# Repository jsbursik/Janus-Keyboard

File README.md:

# Janus Split Ergonomic Keyboard

## Janus

From [Wikipedia](https://en.wikipedia.org/wiki/Janus) on the god Janus: "In ancient Roman religion and myth, Janus (/ˈdʒeɪnəs/ JAY-nəs; Latin: Ianvs [ˈi̯aːnʊs]) is the god of beginnings, gates, transitions, time, duality, doorways, passages, frames, and endings. He is usually depicted as having two faces. The month of January is named for Janus (Ianuarius). According to ancient Roman farmers' almanacs, Juno was mistaken as the tutelary deity of the month of January, but Juno is the tutelary deity of the month of June."

## Motivation

I designed this keyboard after ordering and assembling a [Piantor](https://github.com/beekeeb/piantor) and not really liking the switches and keycaps. After realizing choc switches don't use the normal "+" stems I'm used to and seeing that the choc stems are a bit niche for finding keycaps - I started looking for other low-profile switch options that supported the more ubiquitous "+" stems.

Other issues involved key density, I didn't like how close together everything was. I stretched my fingers out, then closed them up and tried to get a shape that roughly followed the paths of my fingertips. I also added a few more keys than the Piantor has making this a 50 key (25 x 2) keyboard.

In comes the KS27 from Gateron. At one point I had owned a wireless keyboard that used the KS27 Linear Red switches and liked them for the most part, but these days I prefer a more tactile switch (break-over feel without the click). After finding some KS27 Browns on Amazon, I concluded they were what I was looking for. I found the hotswap sockets for the KS27 on Aliexpress and ordered a few hundred to be safe since shipping times were so long. Next I was on the hunt for blank keycaps and found that it was pretty easy to source some blank DSA profile caps from Amazon as well. I haven't used them on a full keyboard yet, but I believe it should be easier to feel out the different keys than the choc low-profile keycaps that came with the Piantor.

## Workflow

I used the web version of Ergogen [here](https://ergogen.cache.works) to get the general shape down until I was ready for all the footprinting and stuff that would have to happen locally. Once I was happy with the general shape, I went through the tedious task of editing footprints and converting them to the `.js` versions that Ergogen expects in the `footprints/` folder. I set up [npm-watch](https://www.npmjs.com/package/npm-watch) (`npm run watch`) to watch out for changes to the `config.yaml` file to automatically run Ergogen. Once everything was placed where I wanted it, I created a `kicad_project` folder separate from the output folder so any Ergogen runs down the road won't effect my work in Kicad (`npm run pcb-update` moves new PCB changes to the `kicad_project` folder). I then routed everything in KiCad version 8, making sure to weave the traces for the reversible nice!nano v2 footprint I made. After everything was routed and the DRC reported no errors, I exported the gerbers and sent them off to JLCPCB. The case was also generated using Ergogen as it's easy enough to do, still working on tweaking some clearances to make everything fit nicely.

## ZMK

This keyboard is meant to use the [nice!nano v2](https://nicekeyboards.com/nice-nano) with the [nice!view screen](https://nicekeyboards.com/nice-view) which means my firmware options were limited as this will be full wireless. The obvious choice feature-wise is ZMK. The documentation is a bit rough around the edges so I've had to do a decent amount of trial and error, as well as researching other ergo keyboard repos to see what they did. The firmware repo for this version of the Janus can be found [here](https://github.com/jsbursik/zmk-janus).

## Parts

| Part                                            | Quantity |
| ----------------------------------------------- | -------- |
| nice!nano v2                                    | 2        |
| sockets/pins for n!n v2                         | 2 sets   |
| nice!view                                       | 2        |
| 5 pin header for nice!view, should come with it | 2 sets   |
| 3.7v Lithium Battery                            | 2        |
| Gateron KS27 Hotswap Sockets                    | 50       |
| Gateron KS27 Low profile Switches               | 50       |
| 1N4148 Diodes (SMD or Thru-hole)                | 100      |
| M2 \* 4mm screws                                | 14       |
| M2 Threaded inserts 2 x 3 x 3.5mm               | 14       |

Other than that, you just need the PCBs and keycaps of your choice.

Links to where I bought my parts:

- [nice!nano v2](https://typeractive.xyz/products/nice-nano)
- [nice!view](https://typeractive.xyz/products/nice-view)
- [sockets/pins](https://typeractive.xyz/products/machine-sockets-and-pins)
- [lithium batteries](https://typeractive.xyz/products/lithium-battery-110mah)
- [Gateron low-profile hot-swap socket](https://www.gateron.com/products/gateron-low-profile-switch-hot-swap-pcb-socket?VariantsId=10234)
- [Gateron KS27 brown switched](https://www.amazon.com/Gateron-ks-27-Switches-Mechanical-Keyboards/dp/B09WYGKDVN/ref=sr_1_1?crid=244VA1GQ1XDVB&dib=eyJ2IjoiMSJ9.Ob91f_tJCQ9o8IUTjbX-EPJT6_KlCjXipGEMMSUyjHpA--qqqJuk777kxlV9F388b-TQxAeNr32AKiCJuMiz9ZiVn6s0R0tHP5klRWKVt7c.dPctAoT2Xv_lhWrQO5m59fR_4n9eiqEAyL8dTO3Mifs&dib_tag=se&keywords=gateron%2Bks27%2Bbrown&qid=1715271708&sprefix=gateron%2Bks27%2Bbrown%2Caps%2C136&sr=8-1&th=1)
- [1N4148WS Surface Mount Diodes x100](https://www.amazon.com/dp/B089KD46P6?psc=1&ref=ppx_yo2ov_dt_b_product_details)
- [M2 screws](https://www.amazon.com/dp/B0BX96SMW4?psc=1&ref=ppx_yo2ov_dt_b_product_details)
- [M2 threaded inserts](https://www.amazon.com/dp/B0B8GN63S2?psc=1&ref=ppx_yo2ov_dt_b_product_details)

## Keymap Layout

This is still very much a work in progress. I've been using the [keymap editor found here](https://nickcoutsos.github.io/keymap-editor/) to try and come up with a barebones setup.

** TODO: add images

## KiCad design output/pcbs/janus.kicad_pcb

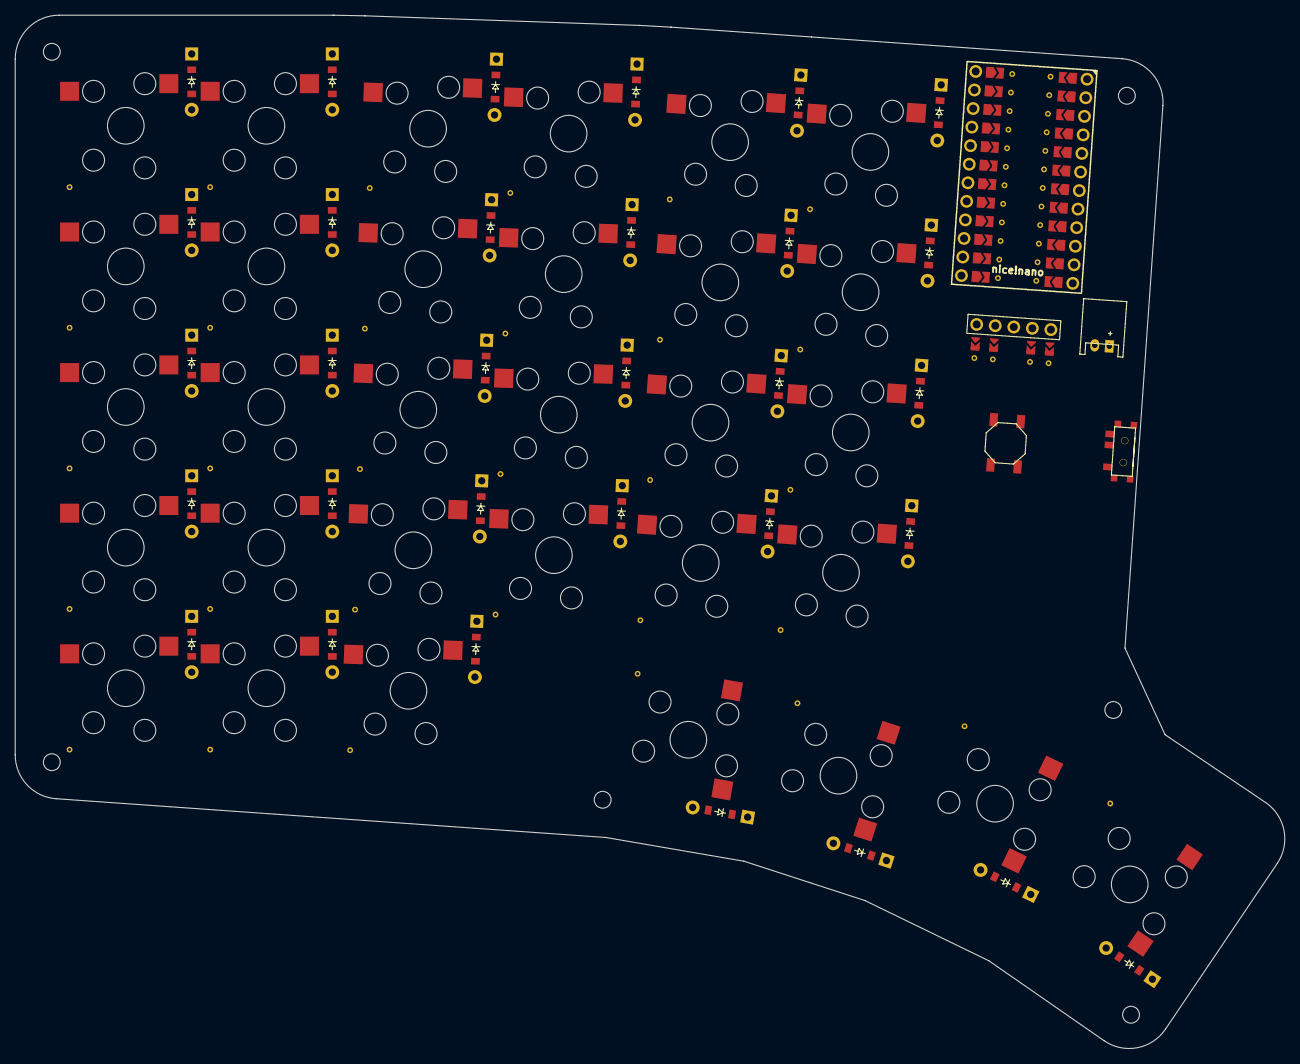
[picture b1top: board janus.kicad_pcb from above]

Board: 2 copper layers, 173.4 x 141.1 mm, 67 parts (0 on the bottom side), 48 nets, no tracks yet.

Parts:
B1: SW_TACT_ALPS_SKQGABE010
D1, D2, D3, D4, D5, D6, D7, D8, D9, D10, D11, D12, D13, D14, D15, D16, D17, D18, D19, D20, D21, D22, D23, D24, D25, D26, D27, D28, D29, D30, D31: ComboDiode
JST1: JST_PH_S2B-PH-K_02x2.00mm_Angled
MCU1: nice!nano_v2
OLED1: nice!view; niceview
S1, S2, S3, S4, S5, S6, S7, S8, S9, S10, S11, S12, S13, S14, S15, S16, S17, S18, S19, S20, S21, S22, S23, S24, S25, S26, S27, S28, S29, S30, S31: ks27; gateron-ks27
T1: SPDT_C128955

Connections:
BPOS: JST1.1, T1.1
GND: B1.1, JST1.2, MCU1.GND
P5: D5.1, D10.1, D15.1, D19.1, D23.1, D27.1, MCU1.P5
P6: D4.1, D9.1, D14.1, D18.1, D22.1, D26.1, MCU1.P6
P7: D3.1, D8.1, D13.1, D17.1, D21.1, D25.1, MCU1.P7
P8: D2.1, D7.1, D12.1, D16.1, D20.1, D24.1, MCU1.P8
P9: D1.1, D6.1, D11.1, D28.1, D29.1, D30.1, D31.1, MCU1.P9
P10: MCU1.P10, S16.1, S17.1, S18.1, S19.1, S28.1
P14: MCU1.P14, S6.1, S7.1, S8.1, S9.1, S10.1
P15: MCU1.P15, S1.1, S2.1, S3.1, S4.1, S5.1
P16: MCU1.P16, S11.1, S12.1, S13.1, S14.1, S15.1
P18: MCU1.P18, S31.1
P19: MCU1.P19, S20.1, S21.1, S22.1, S23.1, S29.1
P20: MCU1.P20, S24.1, S25.1, S26.1, S27.1, S30.1
RAW: MCU1.B+, T1.2
RST: B1.2, MCU1.RST
VCC: MCU1.VCC, OLED1.3
home_cluster: D30.2, S30.2
index_bottom: D20.2, S20.2
index_home: D21.2, S21.2
index_number: D23.2, S23.2
index_top: D22.2, S22.2
inner_bottom: D24.2, S24.2
inner_cluster: D29.2, S29.2
inner_home: D25.2, S25.2
inner_number: D27.2, S27.2
inner_top: D26.2, S26.2
middle_bottom: D16.2, S16.2
middle_home: D17.2, S17.2
middle_number: D19.2, S19.2
middle_top: D18.2, S18.2
mod_cluster: D28.2, S28.2
outer_bottom: D2.2, S2.2
outer_cluster: D31.2, S31.2
outer_home: D3.2, S3.2
outer_mod: D1.2, S1.2
outer_number: D5.2, S5.2
outer_top: D4.2, S4.2
pinky_bottom: D7.2, S7.2
pinky_home: D8.2, S8.2
pinky_mod: D6.2, S6.2
pinky_number: D10.2, S10.2
pinky_top: D9.2, S9.2
ring_bottom: D12.2, S12.2
ring_home: D13.2, S13.2
ring_mod: D11.2, S11.2
ring_number: D15.2, S15.2
ring_top: D14.2, S14.2

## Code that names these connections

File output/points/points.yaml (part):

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        autobind: 10
        skip: false
        asym: both
        colrow: pinky_mod
        name: matrix_pinky_mod
        column_net: P14
        row_net: P9
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        autobind: 10
        skip: false
        asym: both
        colrow: pinky_bottom
        name: matrix_pinky_bottom
        column_net: P14
        row_net: P8
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        autobind: 10
        skip: false
        asym: both
        colrow: pinky_home
        name: matrix_pinky_home
        column_net: P14
        row_net: P7
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        autobind: 10
        skip: false
        asym: both
        colrow: pinky_top
        name: matrix_pinky_top
        column_net: P14
        row_net: P6
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        autobind: 10
        skip: false
        asym: both
        colrow: pinky_number
        name: matrix_pinky_number
        column_net: P14
        row_net: P5
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
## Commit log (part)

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2024-05-13 just the starting template
2024-05-13 making sure the footprints folder exists for the future
2024-05-14 make sure node modules don't upload
2024-05-14 started footprinting and hooking up nets
2024-05-14 added reversible ks27 fp
2024-05-14 added fancy mounting hole from tutorial
2024-05-14 added my reversible NV fp, fixed
2024-05-14 added and finally fixed my custom rev NN fp
2024-05-14 This was to get the nice nano fp started
2024-05-14 generated files
2024-05-15 reversible button fp, original from ergogen
2024-05-15 reversible jstph, original from ergogen
2024-05-15 reversible slider, original from ergogen
2024-05-15 added npm watch
2024-05-15 added watch and pcb-update scripts
2024-05-15 everything placed, sizing tweaked, holes made. Just need a case.
2024-05-15 corrected screw size, added another mount hole
2024-05-15 jumper pads were too close for the DRC
2024-05-15 jumper pads were too close to thruholes for the DRC
2024-05-15 Gerber files for manufacture
2024-05-15 stop uploading zips
2024-05-15 made to match js fp rev_nano
2024-05-15 routed and completed
2024-05-15 no longer uploading backup zips
2024-05-15 generated output
2024-05-15 removing kicad pcb lock file
2024-05-15 shouldn't be in the branch
2024-05-17 added jscad convert
2024-05-17 working on case
2024-05-17 hopefully the final form
2024-05-17 adjusting radii, fixed comments
2024-05-17 fixed holes in PCB manually, generated new gerbers
2024-05-18 New Readme
2024-05-21 updated package lock name
2024-05-21 thicker standoffs, clearance stuff, power slider cutout
2024-06-14 everything needs adjusting, just the beginning
2024-06-14 setup basic layout, made key tester, need to print
2024-06-15 keyplate needed work, dimensions were off
2024-06-16 Removing stagger, testing it out
2024-06-17 supports, adjustments to pcb, good to wire?
2024-06-21 assigned nets, final tweaks to layout
2024-06-23 final routing and generated gerbers
2024-06-29 removed keytester stuff, fixed some outlines, finished the case
